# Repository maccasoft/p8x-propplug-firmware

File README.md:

## P8X Game System PropPlug

USB programming interface for the [P8X Game System](https://dev.maccasoft.com/propgame).

Seen by the operating system as two serial ports compatible with Parallax Prop-plug.

**Windows**
 * GPU_ICSP = COM15
 * CPU_ISCP = COM16

**Linux**
 * GPU_ICSP = /dev/ttyACM0
 * CPU_ISCP = /dev/ttyACM1

_**Note:** Actual port numbers may vary depending on other USB devices plugged on the system._

**Parts List**

 * R1 = 220 ohm 1/4 watt
 * R2 = 220 ohm 1/4 watt
 * R3 = 220 ohm 1/4 watt
 * R4 = 220 ohm 1/4 watt
 * R5 = 33.000 ohm 1/4 watt
 * R6 = 10.000 ohm 1/4 watt
 * R7 = 10.000 ohm 1/4 watt
 * R8 = 10.000 ohm 1/4 watt
 * C1 = 100.000 pF poli
 * C2 = 10 uF 63v elettr.
 * C3 = 22 pF disc
 * C4 = 22 pF disc
 * C5 = 10.000 pF poli
 * DL1 = Red LED
 * DL2 = Yellow LED
 * DL3 = Yellow LED
 * DL4 = Green LED
 * XTAL1 = 12 MHz crystal
 * IC1 = PIC18F24J50
 * TR1 = Transistor BC547
 * CN1 = USB-B connector

PCBs are shared on [OSH Park](https://oshpark.com) and can be ordered from there:  
[https://oshpark.com/shared_projects/9SPZhAax](https://oshpark.com/shared_projects/9SPZhAax)

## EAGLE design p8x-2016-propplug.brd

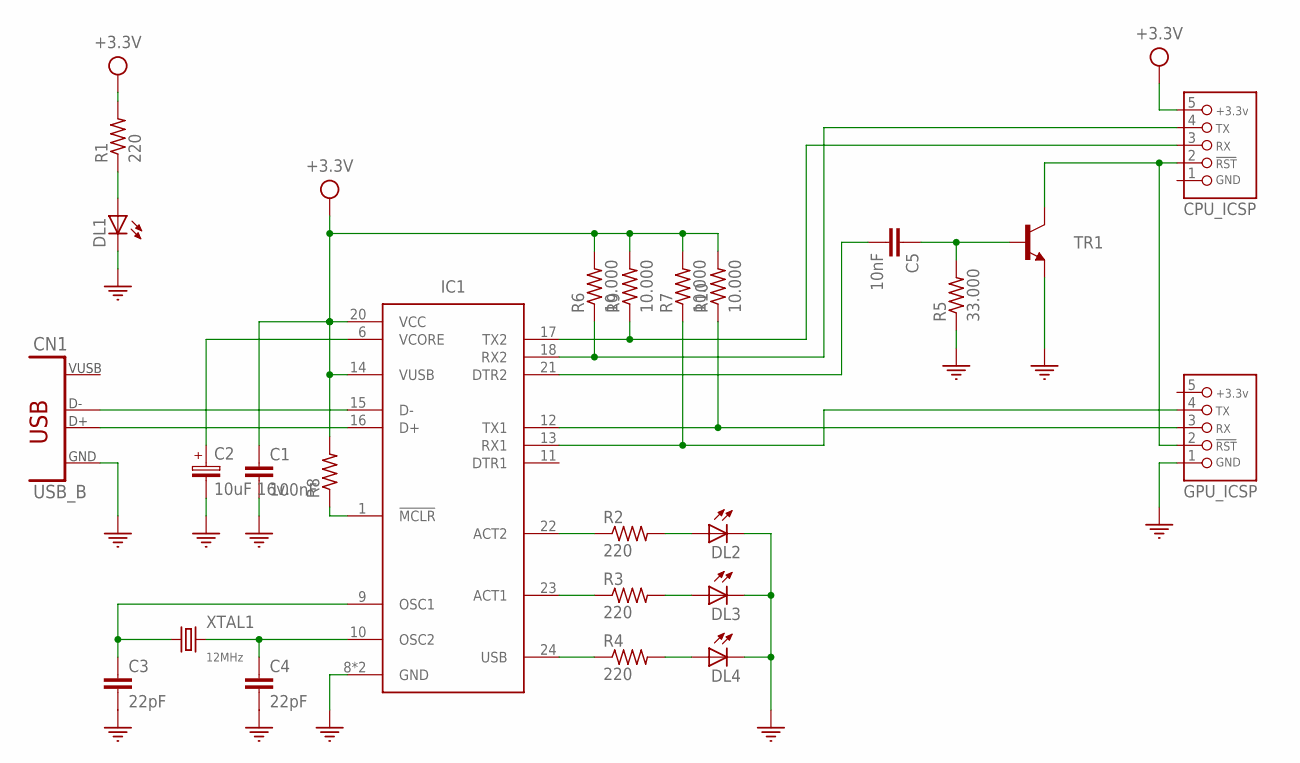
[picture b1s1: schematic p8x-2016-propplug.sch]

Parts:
C1: 100nF; C050-025X075
C2: 10uF 16v.; E2,5-6
C3, C4: 22pF; C050-025X075D
C5: 10nF; C050-025X075
CN1: USB_B; USB-B
CPU_ICSP: PROPELLER_ICSP_HEADER; HEADER_PRG_1X05
DL1, DL2, DL3, DL4: LED-3MM; LED3MM
GPU_ICSP: PROPELLER_ICSP_HEADER; HEADER_PRG_1X05
IC1: PIC18F24J50-I/P; DIL28
R1, R2, R3, R4: 220; 0207/10
R5: 33.000; 0207/10
R6, R7, R9, R10: 10.000; 0207/10
R8: R-1/4W; 0207/10
TR1: BC547; TO92
XTAL1: 12MHz; HC49/S

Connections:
1: CPU_ICSP.1
5: GPU_ICSP.5
!RES1!: C5.2, IC1.21 (DTR2)
+3.3V: C1.1, CPU_ICSP.5, IC1.14 (VUSB), IC1.20 (VCC), R1.2, R6.2, R7.2, R8.2, R9.2, R10.2
ACT1: IC1.23 (ACT1), R3.1
ACT2: IC1.22 (ACT2), R2.1
GND: C1.2, C2.-, C3.2, C4.2, CN1.4 (GND), DL1.K (C), DL2.K (C), DL3.K (C), DL4.K (C), GPU_ICSP.1, IC1.8 (GND), IC1.19 (GND), R5.1, TR1.1 (E)
unnamed: IC1.1 (!MCLR!), R8.1
unnamed: CN1.2 (D-), IC1.15 (D-)
unnamed: CN1.3 (D+), IC1.16 (D+)
unnamed: C4.1, IC1.10 (OSC2), XTAL1.2
unnamed: C3.1, IC1.9 (OSC1), XTAL1.1
unnamed: C5.1, R5.2, TR1.2 (B)
unnamed: DL2.A, R2.2
unnamed: DL3.A, R3.2
unnamed: C2.+, IC1.6 (VCORE)
unnamed: DL4.A, R4.2
unnamed: DL1.A, R1.1
unnamed: CPU_ICSP.2, GPU_ICSP.2, TR1.3 (C)
RX1: CPU_ICSP.4, IC1.18 (RX2), R6.1
RX2: GPU_ICSP.4, IC1.13 (RX1), R7.1
TX1: CPU_ICSP.3, IC1.17 (TX2), R9.1
TX2: GPU_ICSP.3, IC1.12 (TX1), R10.1
USB: IC1.24 (USB), R4.1
VUSB: CN1.1 (VUSB)

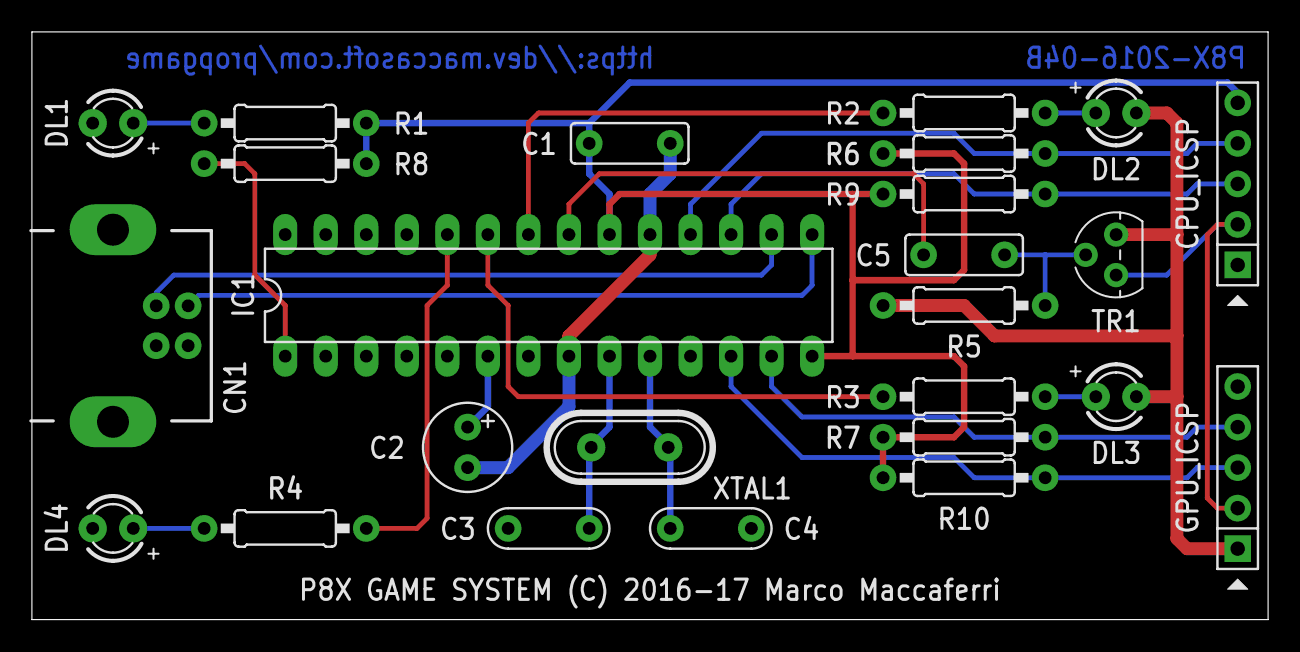
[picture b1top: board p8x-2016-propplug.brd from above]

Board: 2 copper layers, 77.5 x 36.8 mm, 25 parts (0 on the bottom side), 22 nets.

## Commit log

2017-02-19 Optimizations to improve performances
2017-06-16 Updates and fixes for PIC18F24J50
    * Fixed configuration bits
    * TX lines configured as open-drain and added pull-up resistors
    * UART initialization moved at startup
    * Speed optimizations

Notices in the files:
p8x-2016-propplug.brd:
P8X GAME SYSTEM (C) 2016-17 Marco Maccaferri
